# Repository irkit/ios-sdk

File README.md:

IRKit iOS SDK
===

[IRKit device](https://github.com/irkit/device) and SDK(this library) lets you control your home electronics from your iOS devices.
IRKit device has a Infrared LED and receiver, and a WiFi module inside.
Any device with internet or local wifi connection can use IRKit devices to make it send IR signals.

This library does:
* provide UIViewController subclasses that wraps complex procedures to connect and learn IR signals from IRKit devices
* provide a simple interface to send IR signals

## Get IRKit Device

see [IRKit device](https://github.com/irkit/device)

## Installing

Use [cocoapods](http://cocoapods.org/) 1.0.0 or higher  

```sh
$ cat Podfile
source 'https://github.com/CocoaPods/Specs.git'
use_frameworks!

platform :ios, '8.0'
workspace 'MyApp.xcworkspace'
project 'MyApp/MyApp.xcodeproj'

pod 'IRKit', '~> 3.0'

target 'MyApp' do
  project 'MyApp/MyApp.xcodeproj'
end

$ pod install
```

## Usage

See [Minimal app](https://github.com/irkit/ios-sdk/tree/master/Minimal/Minimal) for a working minimal IR remote controller application.

### Include header

```objective-c
#import <IRKit/IRKit.h>
```

### Initialize

```objective-c
- (BOOL)application:(UIApplication *)application didFinishLaunchingWithOptions:(NSDictionary *)launchOptions
{
    [IRKit startWithAPIKey:@"#{ fill in your apikey }"];
    return YES;
}
```

### Get API key

```sh
% curl -d "email={your email}" "http://api.getirkit.com/1/apps"
{"message":"You will receive an email shortly, please click the URL in it to get an apikey"}
```

and open the URL in the email.

### Sending IR signals

IR signal is represented as a  [IRSignal](https://github.com/irkit/ios-sdk/blob/master/IRKit/IRKit/IRSignal.h) instance.

```objective-c
[signal sendWithCompletion:^(NSError *error) {
    NSLog(@"sent error: %@", error);
}];
```

### How to get an IRSignal?

You get your first `IRSignal` by *learning* it, which means: you point your old infrared remote controller at IRKit device's IR receiver, and press it's button.
IRKit device will send it over to your app(with IRKit iOS SDK).

But first, you need to *pair* with an IRKit device.

```objective-c
// in your main view controller
- (void)viewDidAppear:(BOOL)animated {
    [super viewDidAppear:animated];

    // find IRKit if none is known
    if ([IRKit sharedInstance].countOfReadyPeripherals == 0) {
        IRNewPeripheralViewController *vc = [[IRNewPeripheralViewController alloc] init];
        vc.delegate = self;
        [self presentViewController:vc
                           animated:YES
                         completion:^{
                             NSLog(@"presented");
                         }];
    }
}

#pragma mark - IRNewPeripheralViewControllerDelegate

- (void)newPeripheralViewController:(IRNewPeripheralViewController *)viewController
            didFinishWithPeripheral:(IRPeripheral *)peripheral {
    NSLog( @"peripheral: %@", peripheral );

    [self dismissViewControllerAnimated:YES
                             completion:^{
                                 NSLog(@"dismissed");
                             }];
}
```

When pairing is done, you're ready to learn an IRSignal from it.

```objective-c
IRNewSignalViewController *vc = [[IRNewSignalViewController alloc] init];
vc.delegate = self;
[self presentViewController:vc
                   animated:YES
                 completion:^{
                     NSLog(@"presented");
                 }];

#pragma mark - IRNewSignalViewControllerDelegate

- (void)newSignalViewController:(IRNewSignalViewController *)viewController
            didFinishWithSignal:(IRSignal *)signal {
    NSLog( @"signal: %@", signal );

    if (signal) {
        // successfully learned!
        _signal = signal;
    }
    [self dismissViewControllerAnimated:YES
                             completion:^{
                                 LOG(@"dismissed");
                             }];
}

```

### Collection of multiple IRSignals

Most remote controllers have more than 1 button, so you'll want to manage a collection of IRSignals.
`IRSignals` (with a `s` postfix) is it.

```objective-c
_signals = [[IRSignals alloc] init];

// and add a signal to the collection
[_signals addSignalsObject:_signal];

// send multiple IRSignal-s sequentially
[_signals sendSequentiallyWithCompletion:^(NSError *error) {
    NSLog( @"sent with error: %@", error );
}];

// and save it in NSUserDefaults
[_signals saveToStandardUserDefaultsWithKey:@"irkit.signals"];

// or load it from NSUserDefaults
[_signals loadFromStandardUserDefaultsKey:@"irkit.signals"];

// or send it elsewhere
NSData *data = [_signals data];

// or as JSON
NSString *json = [_signals JSONRepresentation];
```

### App Transport Security

IRKit's Device HTTP API doesn't support HTTPS.  
Add following lines in your `Info.plist`.

```xml
	<key>NSAppTransportSecurity</key>
	<dict>
		<key>NSAllowsArbitraryLoads</key>
		<true/>
	</dict>
```

## [Contributing](Contributing.md)

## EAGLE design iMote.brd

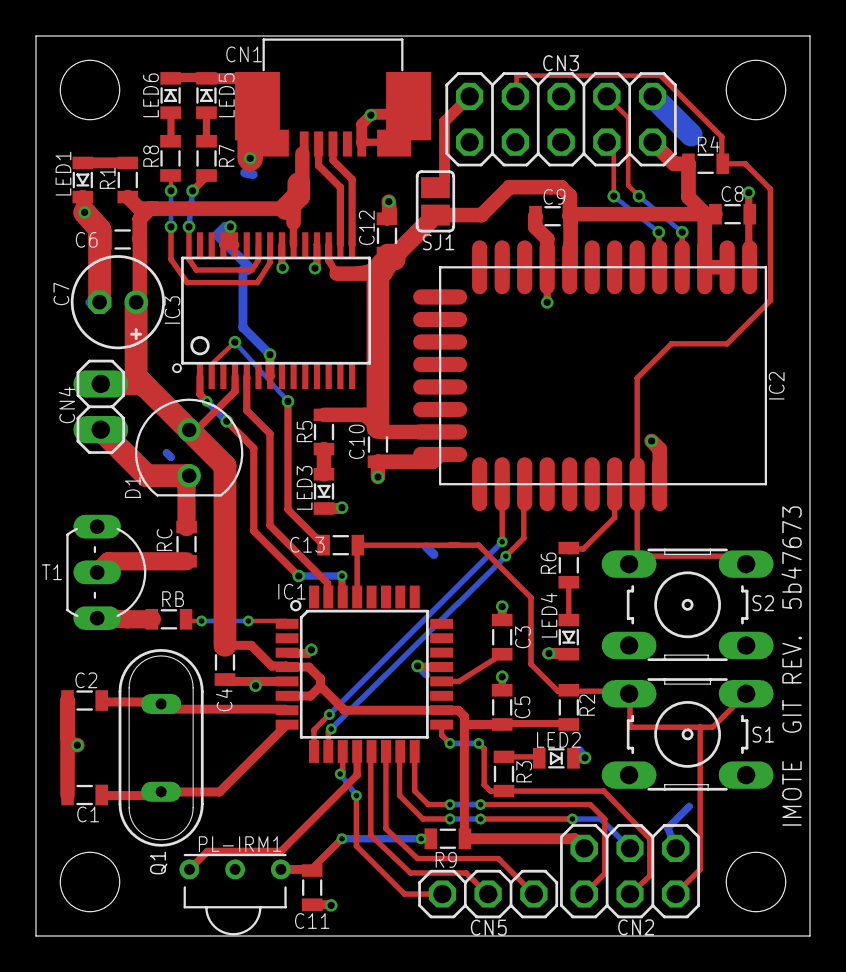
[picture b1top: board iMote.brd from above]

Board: 2 copper layers, 43.0 x 50.0 mm, 50 parts (0 on the bottom side), 39 nets.

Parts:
C1, C2: 22pF; 2012
C3, C4, C5, C6, C8, C9, C10, C12, C13: 0.1uF; 2012
C7: 10uF; E2-5
C11: 4.7uF; 2012
CN1: USB-MINIB-UX60SC-MB
CN2: ICSP; 2X03
CN3: CC-HEADER; 2X05
CN4: 1X02
CN5: PINHEAD-1X03
D1: OSIR5113A; LED-3MM
IC1: ATmega328P-AU; TQFP32-08
IC2: BLE112-A-VISUAL; BLE112-A
IC3: FT232RLSSOP; SSOP28DB
LED1: 5V; LED-2012
LED2: ICSP; LED-2012
LED3: 3.3V; LED-2012
LED4: BLE; LED-2012
LED5: USB/TX; LED-2012
LED6: USB/RX; LED-2012
PL-IRM1: PL-IRM2161; IR-RECEIVER
Q1: 16MHz; XTAL-HC-49/S
R1, R3, R5, R6: 330; 2012
R2, R4: 1K; 2012
R7, R8: 680; 2012
R9: 200; 2012
RB: 4.7k; 2012
RC: 47; 2012
S1, S2: B3F-1000; B3F-10XX
SJ1: 0; SJ
STANDOFF1, STANDOFF2, STANDOFF3, STANDOFF4: STAND-OFF
T1: 2SC1815; TO92-ECB
U$1: 5b47673; GIT-REVISION

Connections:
!BLE/RST: CN3.7, IC2.RESET, R4.1, S2.1, S2.2
!RESET: C13.2, CN2.5, IC1.29, R2.1, S1.1, S1.2
+3V3: C8.1, C9.1, C10.1, C12.1, CN3.2, IC2.AVDD, IC2.AVDD@2, IC2.DVDD, IC2.VDD_USB, IC3.17, R4.2, R5.1, SJ1.2
+5V: C4.2, C5.2, C6.1, C7.+, CN1.VBUS, CN2.2, CN4.1, D1.A, IC1.4, IC1.6, IC1.18, IC3.4, IC3.20, R1.1, R2.2, R9.2
AREF: C3.2, IC1.20
BLE/P0_0: IC2.P0_0, R6.2
BLE/P2_1: CN3.4, IC2.P2_1
BLE/P2_2: CN3.3, IC2.P2_2
D0/USBRX: IC1.30, IC3.1
D1/USBTX: IC1.31, IC3.5
D3/IROUT: IC1.1, RB.2
D5/BLETX: IC1.9, IC2.P0_5
D6/BLERX: IC1.10, IC2.P0_4
D7: CN5.1, IC1.11
D8/IRIN: IC1.12, PL-IRM1.1
D9: CN5.2, IC1.13
D10: CN5.3, IC1.14
D11/MOSI: CN2.4, IC1.15
D12/MISO: CN2.1, IC1.16
D13/SCK: CN2.3, IC1.17, R3.2
GND: C1.1, C2.1, C3.1, C4.1, C5.1, C6.2, C7.-, C8.2, C9.2, C10.2, C11.2, C12.2, CN1.GND, CN1.S$1, CN1.S$1@2, CN1.S$1@3, CN1.S$2, CN1.S$2@2, CN1.S$2@3, CN2.6, CN3.1, IC1.3, IC1.5, IC1.21, IC2.GND, IC2.GND@2, IC2.GND@3, IC2.GND@4, IC3.7, IC3.18, IC3.21, IC3.25, IC3.26, LED1.C, LED2.C, LED3.C, LED4.C, LED5.C, LED6.C, PL-IRM1.2, S1.3, S1.4, S2.3, S2.4, T1.E
IRLED: CN4.2, D1.C, RC.2
unnamed: C1.2, IC1.8, Q1.1
unnamed: C2.2, IC1.7, Q1.2
unnamed: LED1.A, R1.2
unnamed: LED5.A, R7.1
unnamed: LED3.A, R5.2
unnamed: LED6.A, R8.1
unnamed: LED2.A, R3.1
unnamed: C13.1, IC3.2
unnamed: RB.1, T1.B
unnamed: RC.1, T1.C
unnamed: LED4.A, R6.1
unnamed: C11.1, PL-IRM1.3, R9.1
PRG/VDD: CN3.9, SJ1.1
USB/RXLED: IC3.22, R8.2
USB/TXLED: IC3.23, R7.2
USBD+: CN1.D+, IC3.15
USBD-: CN1.D-, IC3.16

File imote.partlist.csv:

"Part";"Value";"Device";"Package";"Description";"MF";"MPN";"OC_FARNELL";"OC_NEWARK";"PROD_ID";
"C1";"22pF";"C-2012";"2012";"CAPACITOR, European symbol";"";"";"";"";"";
"C2";"22pF";"C-2012";"2012";"CAPACITOR, European symbol";"";"";"";"";"";
"C3";"0.1uF";"C-2012";"2012";"CAPACITOR, European symbol";"";"";"";"";"";
"C4";"0.1uF";"C-2012";"2012";"CAPACITOR, European symbol";"";"";"";"";"";
"C5";"0.1uF";"C-2012";"2012";"CAPACITOR, European symbol";"";"";"";"";"";
"C6";"0.1uF";"C-2012";"2012";"CAPACITOR, European symbol";"";"";"";"";"";
"C7";"10uF";"CPOL";"E2-5";"";"";"";"";"";"";
"C8";"0.1uF";"C-2012";"2012";"CAPACITOR, European symbol";"";"";"";"";"";
"C9";"0.1uF";"C-2012";"2012";"CAPACITOR, European symbol";"";"";"";"";"";
"C10";"0.1uF";"C-2012";"2012";"CAPACITOR, European symbol";"";"";"";"";"";
"C11";"4.7uF";"C-2012";"2012";"CAPACITOR, European symbol";"";"";"";"";"";
"C12";"0.1uF";"C-2012";"2012";"CAPACITOR, European symbol";"";"";"";"";"";
"C13";"0.1uF";"C-2012";"2012";"CAPACITOR, European symbol";"";"";"";"";"";
"CN1";"USB-MINIB-UX60SC-MB";"USB-MINIB-UX60SC-MB";"USB-MINIB-UX60SC-MB";"USB-MiniB";"";"";"";"";"";
"CN2";"ICSP";"PINHD-2X3";"2X03";"PIN HEADER";"";"";"";"";"";
"CN3";"CC-HEADER";"PINHD-2X5";"2X05";"PIN HEADER";"";"";"";"";"";
"CN4";"";"PINHD-1X2";"1X02";"PIN HEADER";"";"";"";"";"";
"CN5";"";"PINHEAD-1X03";"PINHEAD-1X03";"PIN HEADER";"";"";"";"";"";
"D1";"OSIR5113A";"LED-3MM";"LED-3MM";"Through-hole LED";"";"";"";"";"";
"IC1";"ATmega328P-AU";"ATMEGA168-AU";"TQFP32-08";"";"";"";"";"";"";
"IC2";"BLE112-A-VISUAL";"BLE112-A-VISUAL";"BLE112-A";"Bluetooth Low Energy single-mode module - Bluetooth 4.0, chip antenna";"";"";"";"";"";
"IC3";"FT232RLSSOP";"FT232RLSSOP";"SSOP28DB";"USB UART";"";"";"";"";"IC-00870";
"LED1";"5V";"LED-2012";"LED-2012";"Through-hole LED";"";"";"";"";"";
"LED2";"ICSP";"LED-2012";"LED-2012";"Through-hole LED";"";"";"";"";"";
"LED3";"3.3V";"LED-2012";"LED-2012";"Through-hole LED";"";"";"";"";"";
"LED4";"BLE";"LED-2012";"LED-2012";"Through-hole LED";"";"";"";"";"";
"LED5";"USB/TX";"LED-2012";"LED-2012";"Through-hole LED";"";"";"";"";"";
"LED6";"USB/RX";"LED-2012";"LED-2012";"Through-hole LED";"";"";"";"";"";
"PL-IRM1";"PL-IRM2161";"PL-IRM2161";"IR-RECEIVER";"PL-IRM2161-XD1";"";"";"";"";"";
"Q1";"16MHz";"XTAL-HC-49/S";"XTAL-HC-49/S";"CRYSTAL";"";"";"";"";"";
"R1";"330";"R";"2012";"RESISTOR";"";"";"";"";"";
"R2";"1K";"R";"2012";"RESISTOR";"";"";"";"";"";
"R3";"330";"R";"2012";"RESISTOR";"";"";"";"";"";
"R4";"1K";"R";"2012";"RESISTOR";"";"";"";"";"";
"R5";"330";"R";"2012";"RESISTOR";"";"";"";"";"";
"R6";"330";"R";"2012";"RESISTOR";"";"";"";"";"";
"R7";"680";"R";"2012";"RESISTOR";"";"";"";"";"";
"R8";"680";"R";"2012";"RESISTOR";"";"";"";"";"";
"R9";"200";"R";"2012";"RESISTOR";"";"";"";"";"";
"RB";"4.7k";"R";"2012";"RESISTOR";"";"";"";"";"";
"RC";"47";"R";"2012";"RESISTOR";"";"";"";"";"";
"S1";"B3F-1000";"10-XX";"B3F-10XX";"OMRON SWITCH";"";"B3F-1000";"176432";"36M3542";"";
"S2";"B3F-1000";"10-XX";"B3F-10XX";"OMRON SWITCH";"";"B3F-1000";"176432";"36M3542";"";
"SJ1";"0";"SJ";"SJ";"SMD solder JUMPER";"";"";"";"";"";
"STANDOFF1";"STAND-OFF";"STAND-OFF";"STAND-OFF";"#4 Stand Off";"";"";"";"";"";
"STANDOFF2";"STAND-OFF";"STAND-OFF";"STAND-OFF";"#4 Stand Off";"";"";"";"";"";
"STANDOFF3";"STAND-OFF";"STAND-OFF";"STAND-OFF";"#4 Stand Off";"";"";"";"";"";
"STANDOFF4";"STAND-OFF";"STAND-OFF";"STAND-OFF";"#4 Stand Off";"";"";"";"";"";
"T1";"2SC1815";"2SC1815";"TO92-ECB";"NPN EPITAXIAL TRANSISTOR";"";"";"";"";"";
"U$1";"5b47673";"GIT-REVISION";"GIT-REVISION";"";"";"";"";"";"";

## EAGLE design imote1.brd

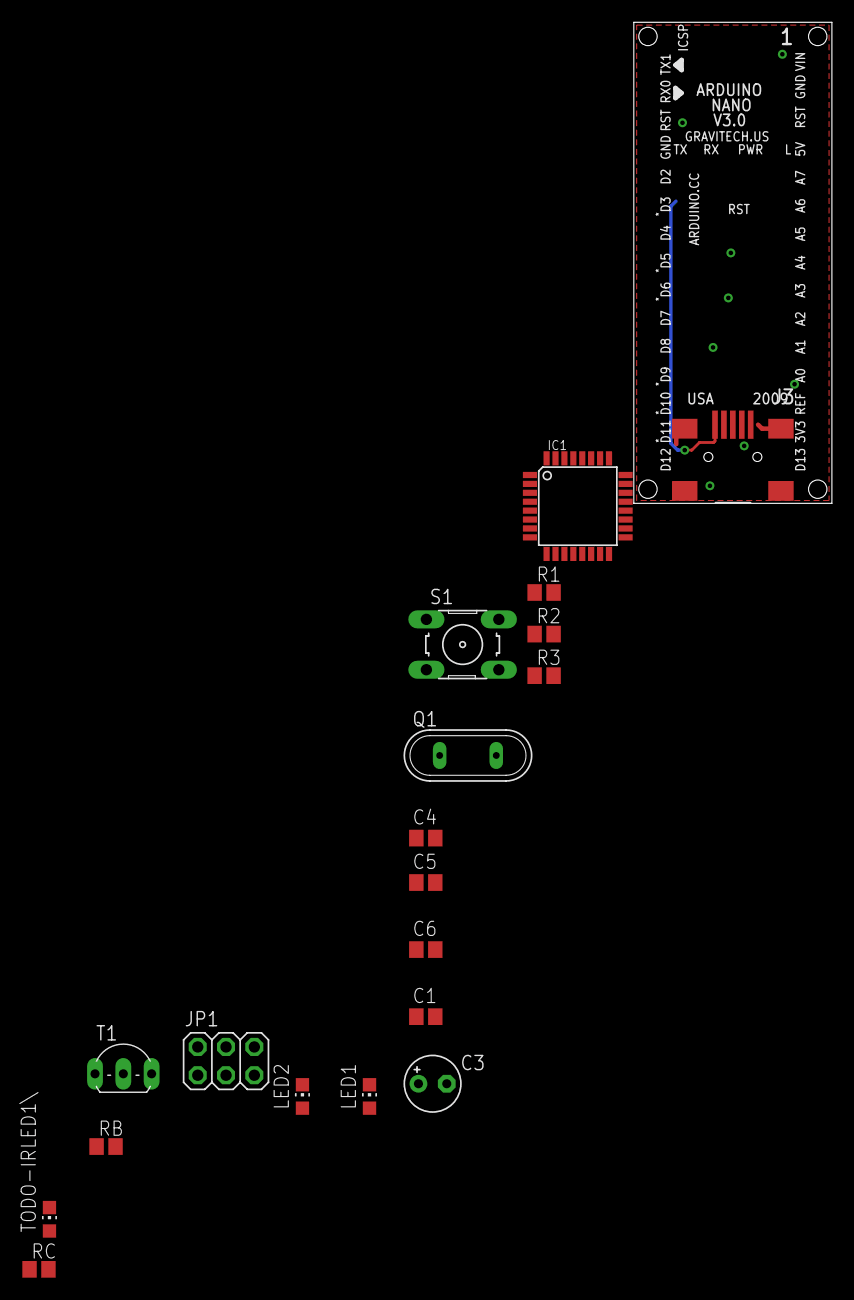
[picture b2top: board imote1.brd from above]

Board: 2 copper layers, 17.8 x 43.2 mm, 19 parts (0 on the bottom side), 13 nets.

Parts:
C1, C6: 0.1uF; C2012
C3: 10uF; E2,5-5
C4, C5: 22pF; C2012
IC1: ATmega328P-AU; TQFP32-08
J3: USB-MINI-B%C; USB-MINI-B_2
JP1: 2X03
LED1, LED2: CHIP-LED0805
Q1: 16MHz; QS
R1: 1K; R2012
R2, R3: 330; R2012
RB: 4.7k; R2012
RC: 47; R2012
S1: B3F-1000; B3F-10XX
T1: 2SC1815; TO92-ECB
TODO-IRLED1\: CHIP-LED0805

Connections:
!RESET: IC1.29, R1.1, S1.1, S1.2
+5V: C1.1, C3.+, IC1.4, IC1.6, IC1.18, J3.5, JP1.2, R1.2, R3.1, TODO-IRLED1\.A
AREF: C6.2, IC1.20
D9/IROUT: IC1.13, RB.2
D12/MISO: IC1.16, JP1.1
GND: C1.2, C3.-, C4.1, C5.1, C6.1, IC1.3, IC1.5, IC1.21, J3.1, J3.6, J3.7, J3.8, J3.9, JP1.6, LED1.C, LED2.C, S1.3, S1.4, T1.E
unnamed: C4.2, IC1.8, Q1.1
unnamed: C5.2, IC1.7, Q1.2
unnamed: LED1.A, R3.2
unnamed: LED2.A, R2.1
unnamed: RB.1, T1.B
unnamed: RC.1, T1.C
unnamed: RC.2, TODO-IRLED1\.C

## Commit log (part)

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2013-08-05 json encode irsignals array into custom scheme url. app handles the custom scheme and inflates signals into tableview and sends it (not implemented)
2013-08-05 forget about "signals", server only knows "query"
2013-08-05 refactoring icon upload
2013-08-05 receives irsignals and icon image as multipart form-data
2013-08-05 applied design into IRPeripheralCell
2013-08-05 ios side connects when app becomes active, and retains connection while active, and disconnects when going background (if retainConnectionInBackground)
2013-08-05 Signals refactored to Query
2013-08-05 make cpp -> c if we can
2013-08-05 peripheral notifies unread statuc c12c when received ir data (doesn't use advertisement data) ios reads ir data when receiving notification
2013-08-05 sendSequentially works
2013-08-05 creating signal name edit (IRNewSignalScene2) view controller
2013-08-05 customize views in one place: IRViewCustomizer
2013-08-05 make the tableview grouped, to unfix our headerview
2013-08-05 update images from shiiho
2013-08-05 draw chartview with 1px line
2013-08-05 updated IRNewPeripheralScene3, IRNewSignalScene2
2013-08-05 html, css for show.template
2013-08-05 refactor scene3
2013-08-05 style
2013-08-05 show network error
2013-08-05 don't show "unknown name"
2013-08-05 fix title
2013-08-05 since appengine filters http response, probably monitoring Location header's length, we can't directly redirect with http status 302 to data scheme. so we use javascript:location.href to redirect to 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
2013-08-05 skip deploying images/
2013-08-05 make base url const
2013-08-05 fix test, works fine on appengine too
2013-08-05 refactored * removed Config and provide imagedirectory from main, which appengine doesn't run
2013-08-05 make menu view controller's cell's bottom border 0.5px
2013-08-05 fix sequential xmit. sequential xmit fails when new irdata arrives to BLE112 while IrCtrl.state is still xmitting. so we delay responding to write requests til IrCtrl.state becomes idle
2013-08-05 SimpleRemote -> One
2013-08-05 refactor to let developers write less code to use IRKit
2013-08-05 .sch & .brd & .3dm & .stl make a modification.
2013-08-08 always connect to a peripheral which uuid is nil
2013-08-08 cleanup
2013-08-08 temporary toggle to fix circuit's wrong wiring show green on clean startup
2013-08-08 led can blink
2013-08-08 fix unsaved bug
2013-08-08 better UI..
2013-08-08 give title parameter to set title
2013-08-08 apply design to webview
2013-08-08 fix test write.js is not used anymore
2013-08-08 user might have already connected their peripheral, so our NewPeripheral scanner uses already connected but non authorized peripheral
2013-08-08 initial Minimal project import
2013-08-08 simpler sdk interface
2013-08-08 make icon roundrect
2013-08-08 show a name for each icons
2013-08-08 coding...
2013-08-08 what?
2013-08-08 rounded corners for icon
2013-08-08 IRKit instance doesn't scan automatically, IRNewPeriphrealVC does
2013-08-08 added LICENSE for each major subdirs, and removed license header from each files
2013-08-08 layout
2013-08-08 remove files from .pch to prepare for cocoapods
2013-08-08 turn on more warnings and clear them
2013-08-08 fix test, and ViewSample compile error
2013-08-08 updated images by shiiho
2013-08-08 Found and fixed a leak in KVO > An instance 0x8e32530 of class IRPeripheral was deallocated while key value observers were still registered with it. Observation info was leaked, and may even become m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
2013-08-09 fix crash bug that calls removeObserver:forKeyPath: again
2013-08-13 Let's use Proximity Authentication Service(original), when peripheral and central is close enough, we authenticate
2013-08-14 re-scan when iOS's bluetooth daemon dies when scanning
2013-08-20 ir-state moved to device/
2013-08-21 follow device's bdca912c117d6f68c56ac70c5fa255da0f61f5de commit
2013-08-21 authorize -> authenticate
2013-10-08 created morse sound player using NSOperation
2013-10-09 wps -> wpm (words per minute)
2013-10-12 enable changing wpm
2013-10-17 normal morse works with AUGraph
2013-10-17 use monoral
2013-11-07 use hex+/ specialized morse table
2013-11-07 these hacks might be unnecessary on iOS7
2013-11-17 IRWifiEdit in conjunction with IRSecuritySelect sets IRKeys model
2013-11-18 fixed IRNewPeripheralScene2
2013-11-21 send wifi and key for IRKit using morse works!!
2013-11-22 let's use ISHTTPOperation
2013-11-22 polls POST /door while waiting for IRKit to connect to wifi
2013-11-26 many many updates
2013-11-29 we might want to transfer more in the future (like static IP), so prepare reserved state future iOS and firmware can support more parameters, while still supporting old firmware
2013-11-29 remove unused
2013-12-01 viewsamples needs libPods too
2013-12-02 applying new design
2013-12-02 parse JSON in http client
2013-12-03 many more features
2013-12-04 building wait for signal
2013-12-04 it's more simple to make signal.frequency NSNumber
2013-12-04 receiving signal works
2013-12-05 apply design to scene1
2013-12-05 apply design for IRMorsePlayerVC
2013-12-05 many improvements
2013-12-06 refactor
2013-12-06 show Start button if volume is max
2013-12-06 check validness of password for wep security type
2013-12-06 more localize and apply design
2013-12-07 show animation when morse starts playing
2013-12-07 added tabbar images
2013-12-09 we don't need another webviewcontroller
2013-12-09 peripheral.asDictionary is for debug
2013-12-09 fix bug that 2 rows of "Find New IRKit" shows up in settings
2013-12-09 usability
2013-12-10 added code to request POST /register
2013-12-10 build samples again
2013-12-10 follow server update
2013-12-10 l10n
2013-12-10 added "802.11b,g,n only"
2013-12-10 add clear=1 only on the 1st GET /messages request
2013-12-10 5 seems to be too short, iOS returns 404?
2013-12-18 fix fetching hostInfo
2013-12-18 refactor error handling, if requests against our server on internet responds with error, show alert dialog
2013-12-18 use const
2013-12-18 moved image loader from helper to httpclient
2013-12-28 fix podspec
2014-01-01 use /1/ api endpoints
2014-01-01 make cocoapods generate IRKitResources target
2014-01-03 avoid calling ensureRegisteredAndCall: 3 times in a row on startup
2014-01-05 there was no such IRSignals sendWithCompletion
2014-01-05 document follow master
2014-01-05 let's leave super
2014-01-05 new IRWifiAdhocViewController to guide user to connect to IRKitXXXX adhoc wifi network
2014-01-05 fixing adhoc route, it's working now!
2014-01-05 only show it the 2nd time user visits MorsePlayerViewController
2014-01-05 warn if ipad
2014-01-05 avoid nested push animation can result in corrupted navigation bar Finishing up a navigation transition in an unexpected state. Navigation Bar subview tree might get corrupted.
2014-01-06 fix warning
2014-01-06 works without calling these audiosession deprecated calls
2014-01-06 prepend fadein envelope to make sound mild, and device stable to recognize
2014-01-06 make cancellable from IRSignalNameEditViewController
2014-01-06 cleanup interface
2014-01-06 avoid leak carefully
2014-01-08 comments and logs
2014-01-16 if security is WEP, crc must be calculated using HEX representation of ASCII password
2014-01-28 alert if ssid or password includes ","
2014-01-28 rebuild
2014-02-11 detect country by carrier and locale
2014-02-17 more comments about dictionary
2014-02-17 created test case for IRSignal
2014-02-17 JSON representation uses "freq" as key for frequency, because IRKit device http api GET /messages responds with that.
2014-02-17 uncrustify
    align_oc_msg_colon_span
    indent_oc_block
    newline before else
2014-02-17 sp_after_oc_dict_colon
2014-02-20 uncrustify
2014-02-20 move waitForSignalWithCompletion to view *Did* Appear, because if 401 happens (like it does in viewSamples), it automatically calls [_self cancelButtonPressed: nil]; before viewDidAppear, which corru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
2014-02-20 test http with OHHTTPStubs
2014-02-20 test .data and loadFromData recovers
2014-02-20 IRSignals can container IRSignal and IRSignalSequence. Move common methods into IRSendable protocol. IRSignals is used to persist collection of IRSignal and IRSignalSequence. Sending methods moved to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
2014-02-20 name and custom property also exists in IRSignalSequence
2014-03-05 renaming - IRNewPeripheralScene1 -> IRGuidePower - IRNewPeripheralScene2,IRWifiAdhoc -> IRGuideWifi
2014-03-05 don't retry infinitely if bug or in IRKitViewSamples app
2014-03-06 don't DOS
2014-03-06 make autolayout work beautifully in 3.5inch iPhone too
2014-03-06 appy backgroundColor change (by shiiho)
2014-03-06 remove morse related things
2014-03-17 limitedAP route looks pretty simple and works
2014-03-17 hide HUD before showing HUD to avoid double showing
2014-03-17 added circular background image for IRProgressView
2014-03-17 added tests
2014-03-17 switch from Reachability to IRReachability
2014-03-17 follow recommended project settings
2014-03-20 some people don't understand "ネットワーク名"
2014-03-24 auto inflate current connected SSID
2014-04-04 no one was using variable args for IRKitLog anyway
2014-04-04 why weren't we?
2014-04-04 make IRSignalSequence available importing IRKit.h
2014-04-05 Always wait for /1/door, because POST /wifi might not respond with status code 200 even AVR has received correct Wi-Fi information. Unfortunately our GS module is not stable. So even if POST /wifi lo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
2014-04-05 Make progressview not cover navigationbar, to let user to go back to check password and restart if they wish. Timeout after 30sec and alert to try again.
2014-04-10 not "Done" but "Next" in IRGuidePowerViewController
2014-04-10 fix to run all view controllers without errors
2014-04-10 fix bug that it shows alert twice, and when user taps 2nd alert, app crashes because it's delegate (IRGuideWifiViewController) is released already
2014-04-11 rebuilt
2014-04-15 remove unnecessary dependency
2014-04-16 more comments
2014-04-20 fix warnings
2014-04-21 public URL for recommended apps
2014-05-02 emphasis to shortly press remotes button
2014-05-27 If we're connected to a network name starting with "IRKit", ignore it. We're probably retrying while already connected to IRKitXXXX access point.
2014-05-27 Fix crash at -[UIAlertView modalItem:shouldDismissForButtonAtIndex:] + 62 Be sure to clear alertView.delegate before viewcontroller's dealloc
2014-06-06 return customizedName too
2014-06-06 Introduced indexOfObject, for use in Mac app. peripherals are now sorted by first found date.
2014-06-24 Expose searching state
2014-06-25 Well..
2014-07-14 Better alert message, and rebuild bundle.
2014-07-23 Remember which regdomain we used to setup (for debug purpose only)
2014-08-11 Introduce clearPeripherals
2014-11-27 More convenient methods to save
2014-11-27 Post notification after clientkey is set
2015-03-04 refresh deviceid, in case the IRKit had been reset and re-setup and has a different devicekey.
2015-03-04 Build safely when linked with app extension, if TARGET_IS_EXTENSION is defined
2015-07-08 Add X-Requested-With header
2015-11-30 IRKit supports osx platform, but with limited source files
2015-11-30 And more
2016-07-08 Tweak for recent cocoapods
2016-07-08 Add App Transport Security settings for minimal project
2016-07-08 Fix build error due to enum definition
2016-07-08 Fix again error: include of non-modular header inside framework module
2016-07-08 Dropping osx support to satisfy pod lib lint
2016-07-08 use_frameworks! to use @import ISHTTPOperation
2016-07-08 version++
2016-07-08 Fix mode
2016-11-27 Since we're used also in extensions, remove code directly using UIApplication.sharedApplication, and so on
2016-11-27 Follow Xcode recommendations and rebuild

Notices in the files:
parts and their libraries:
SparkFun-Electromechanical: Licensing: CC v3.0 Share-Alike You are welcome to use this library for commercial purposes.
